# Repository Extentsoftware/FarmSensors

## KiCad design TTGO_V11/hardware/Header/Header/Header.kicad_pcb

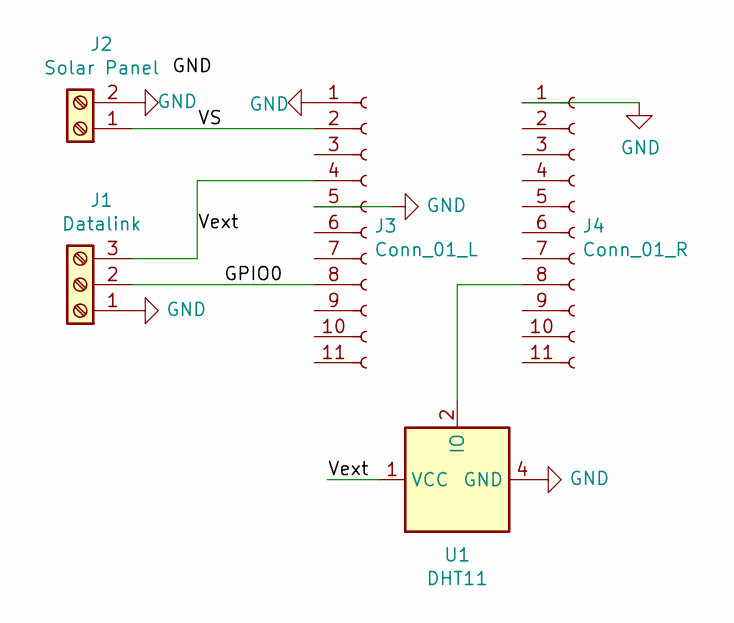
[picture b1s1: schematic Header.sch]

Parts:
J1: Datalink; TerminalBlock_MetzConnect_Type101_RT01603HBWC_1x03_P5.08mm_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
J2: Solar Panel; TerminalBlock_MetzConnect_Type101_RT01602HBWC_1x02_P5.08mm_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
J3: Conn_01_L; PinHeader_1x11_P2.54mm_Vertical
J4: Conn_01_R; PinHeader_1x11_P2.54mm_Vertical
U1: DHT11; Aosong_DHT11_5.5x12.0_P2.54mm

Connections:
/GPIO0: J1.2, J3.8
/VS: J2.1, J3.2
/Vext: J1.3, J3.4, U1.1 (VCC)
GND: J1.1, J2.2, J3.1, J3.5, J4.1, U1.4 (GND)
unnamed: J4.8, U1.2 (IO)

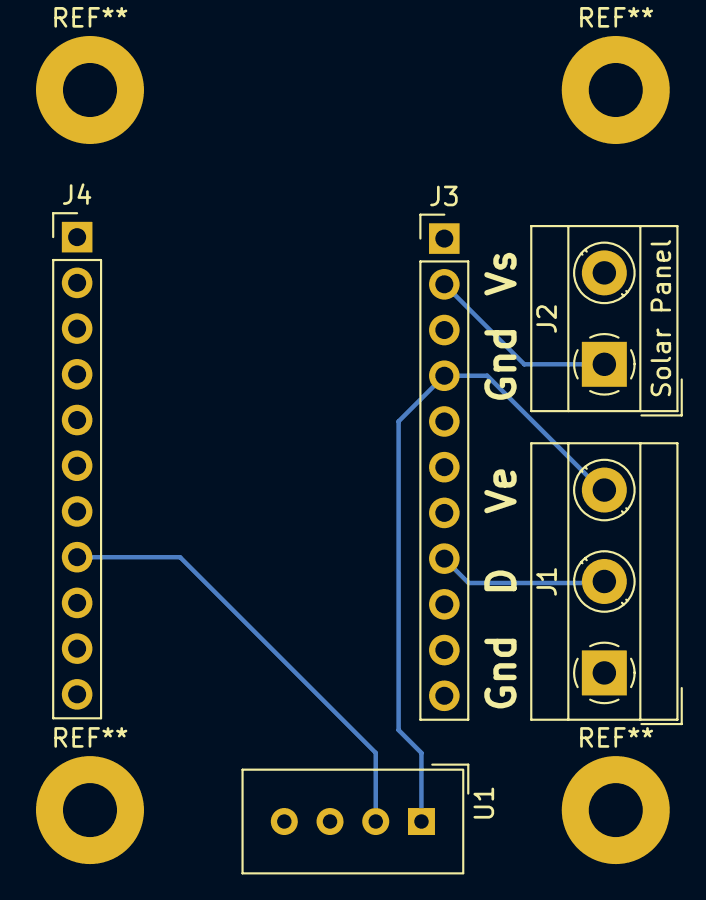
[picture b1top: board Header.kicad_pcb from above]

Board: 2 copper layers, 5 parts (0 on the bottom side), 5 nets.

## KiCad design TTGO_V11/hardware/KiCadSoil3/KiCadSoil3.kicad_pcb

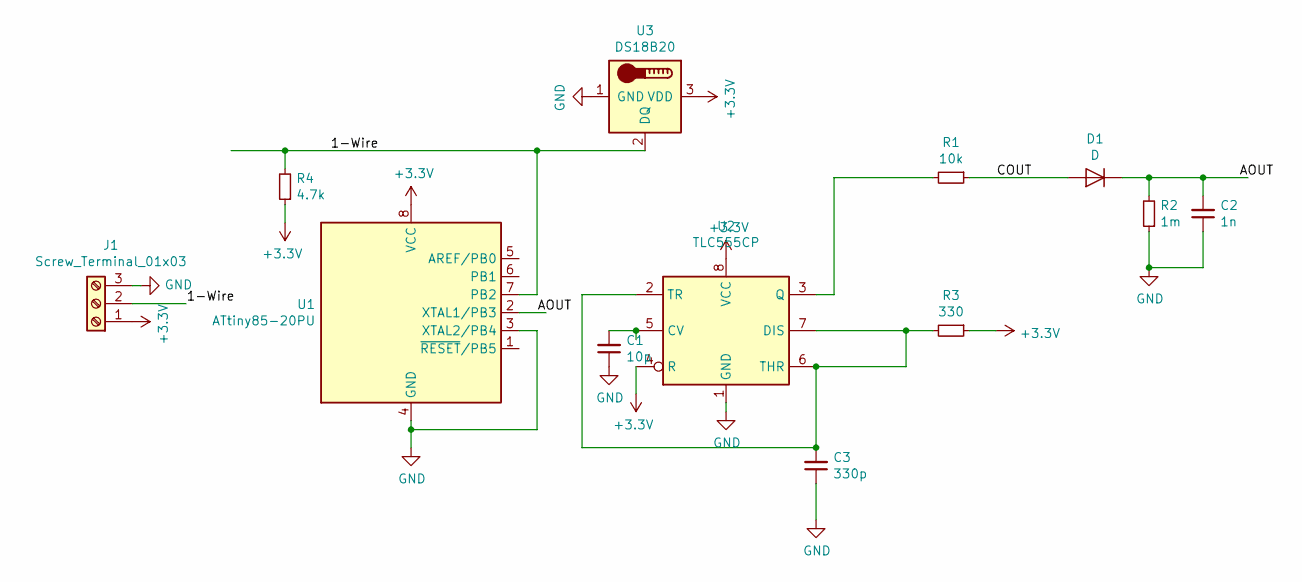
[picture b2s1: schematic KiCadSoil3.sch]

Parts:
C1: 10p; C_Disc_D4.3mm_W1.9mm_P5.00mm
C2: 1n; C_Disc_D4.3mm_W1.9mm_P5.00mm
C3: 330p; C_Disc_D4.3mm_W1.9mm_P5.00mm
D1: D; D_T-1_P5.08mm_Horizontal
J1: Screw_Terminal_01x03; JST_EH_B3B-EH-A_1x03_P2.50mm_Vertical
R1: 10k; R_Axial_DIN0204_L3.6mm_D1.6mm_P7.62mm_Horizontal
R2: 1m; R_Axial_DIN0204_L3.6mm_D1.6mm_P7.62mm_Horizontal
R3: 330; R_Axial_DIN0204_L3.6mm_D1.6mm_P7.62mm_Horizontal
R4: 4.7k; R_Axial_DIN0204_L3.6mm_D1.6mm_P7.62mm_Horizontal
U1: ATtiny85-20PU; DIP-8_W7.62mm
U2: TLC555CP; DIP-8_W7.62mm
U3: DS18B20; TO-92_Inline_Wide

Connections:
+3V3: J1.1, R3.1, R4.1, U1.8 (VCC), U2.4 (R), U2.8 (VCC), U3.3 (VDD)
/1-Wire: J1.2, R4.2, U1.7 (PB2), U3.2 (DQ)
/AOUT: C2.2, D1.1 (K), R2.2, U1.2 (XTAL1/PB3)
/COUT: D1.2 (A), R1.1
GND: C1.1, C2.1, C3.1, J1.3, R2.1, U1.3 (XTAL2/PB4), U1.4 (GND), U2.1 (GND), U3.1 (GND)
unnamed: C1.2, U2.5 (CV)
unnamed: C3.2, R3.2, U2.2 (TR), U2.6 (THR), U2.7 (DIS)
unnamed: R1.2, U2.3 (Q)

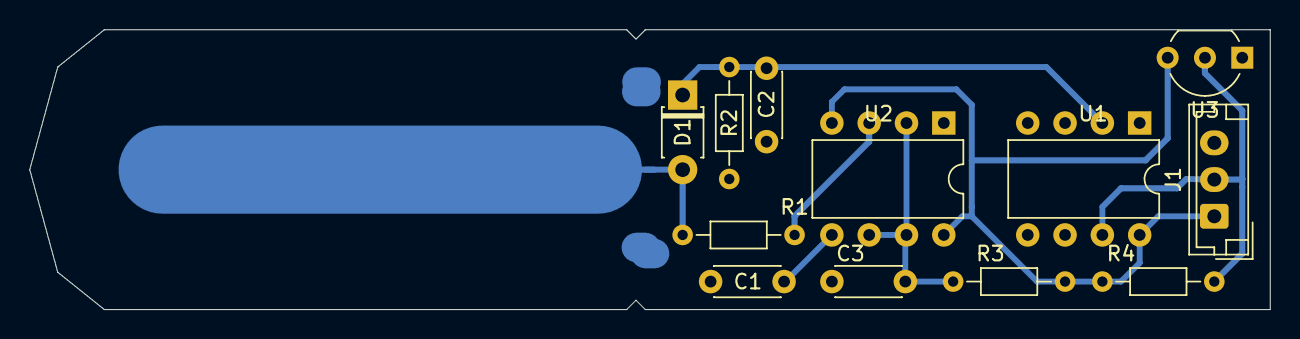
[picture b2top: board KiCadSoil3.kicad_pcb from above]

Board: 2 copper layers, 84.5 x 19.0 mm, 12 parts (0 on the bottom side), 8 nets.

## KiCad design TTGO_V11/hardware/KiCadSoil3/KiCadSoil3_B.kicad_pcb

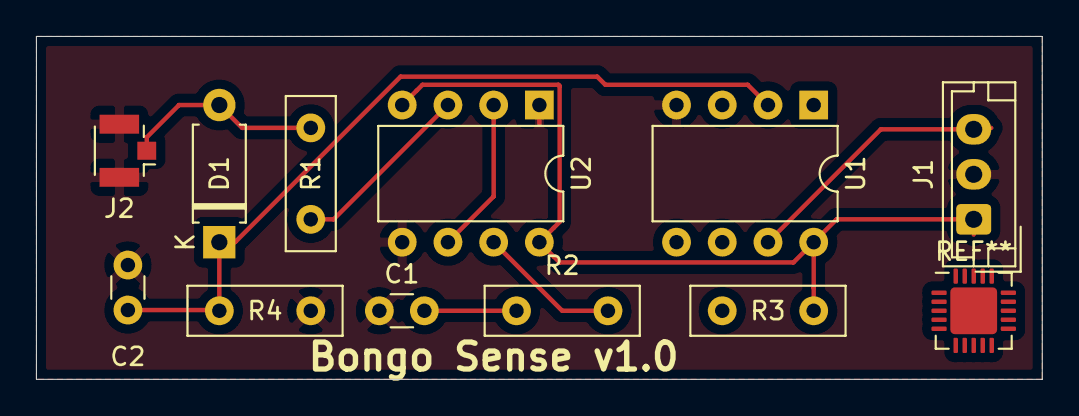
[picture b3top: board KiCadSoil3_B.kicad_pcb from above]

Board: 2 copper layers, 55.9 x 19.1 mm, 11 parts (0 on the bottom side), 9 nets.

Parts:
C1, C2: 660p; C_Disc_D3.0mm_W1.6mm_P2.50mm
D1: D; D_A-405_P7.62mm_Horizontal
J1: Screw_Terminal_01x03; JST_EH_B3B-EH-A_1x03_P2.50mm_Vertical
J2: Conn_Coaxial; U.FL_Hirose_U.FL-R-SMT-1_Vertical
R1: 10k; R_Box_L8.4mm_W2.5mm_P5.08mm
R2: 1.6k; R_Box_L8.4mm_W2.5mm_P5.08mm
R3: 330; R_Box_L8.4mm_W2.5mm_P5.08mm
R4: 1m; R_Box_L8.4mm_W2.5mm_P5.08mm
U1: ATtiny85-20PU; DIP-8_W7.62mm
U2: TLC555CP; DIP-8_W7.62mm

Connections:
+3V3: J1.1, R3.1, U1.8, U2.4, U2.8
/1-Wire: J1.3, U1.7
/AOUT: C2.2, D1.1, R4.2, U1.2
GND: C1.1, C2.1, J1.2, J2.2, R4.1, U1.4, U2.1, U2.5
unnamed: C1.2, R2.1
unnamed: D1.2, J2.1, R1.1
unnamed: R1.2, U2.3
unnamed: R2.2, R3.2, U2.7
unnamed: U2.2, U2.6

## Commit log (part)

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2019-07-03 initial
2019-07-03 started readme
2019-07-04 preferences
2019-07-05 sensor work
2019-07-06 tiny gps work
2019-07-06 fixed build
2019-07-10 sensor
2019-07-10 moved to platformio
2019-07-10 more platform.io work
2019-07-10 platform work
2019-07-10 added library
2019-07-11 change startup modes
2019-07-11 new modes
2019-07-11 typos
2019-07-11 docs
2019-07-12 updated docs
2019-07-12 readme
2019-07-21 library dependencies
2019-07-21 start on sensor UI
2019-07-21 fix radio xmit
2019-07-21 complete web form config
2019-07-21 send diagnostics
2019-07-22 startup modes for hub
2019-07-22 included power settings
2019-07-23 board changes
2019-07-23 fixed defaults
2019-07-25 rearranged lora startup
2019-07-27 testbed
2019-07-28 working 125khz, sf6/cr5
2019-07-28 migrated radio settings to main project
2019-07-28 Adjusted power settings
2019-08-01 hardware changes
2019-08-01 debug
2019-08-02 changed to 15min broadcast
2019-08-05 changed modes on hub
2019-08-06 implemented wifi toggle
2019-08-07 tidyup
2019-08-10 move pwr to gpio4
2019-08-11 sensor changes
2019-08-13 startup changes
2019-08-13 beast 2 setup
2019-08-15 move to i2c
2019-08-16 i2c work
2019-08-21 biard
2019-08-22 wake up time issues
2019-08-30 set correct delay for temp sensor
2019-09-10 reorganise for two TTGO board types
2019-09-10 axp changes
2019-09-11 axp192 work
2019-09-11 power library
2019-09-11 fixed gps wakeup
2019-09-12 power experiments
2019-09-13 gitignore
2019-09-13 power changes
2019-09-13 introduce power into v10 hub
2019-09-13 power changes to the hub
2019-09-13 updated readne
2019-09-15 removed redundant files
2019-09-20 hub version and gps diagnostics
2019-09-24 cleanup
2019-10-13 power mode
2019-10-13 hub wifi timeout
2020-02-25 update libs
2020-03-27 capability
2020-04-25 fix sensors
2020-05-16 Delays
2020-07-08 display changes
2020-07-10 mqtt work
2020-07-16 reorg boards
2020-07-23 add wifi
2020-08-31 added ds18b20
2020-11-20 reconfigure
2020-11-21 header working
2020-11-26 onewire work
2020-12-21 new at85ADC
2020-12-22 added oscillator
2020-12-24 generic adc + frequency counter
2020-12-24 message
2021-01-11 sensor board work
2021-02-21 drill
2021-04-10 new board
2021-04-20 fix hub
2021-04-23 mods
2021-04-26 implement wifi mode
2021-04-28 include dallas
2021-04-28 add dallas
2021-05-15 design changes
2021-05-16 pcb changes
2021-05-18 drill hole changes
2021-06-19 organise folders
2021-06-19 Bump lodash
    Bumps [lodash](https://github.com/lodash/lodash) from 4.17.11 to 4.17.21.
    - [Release notes](https://github.com/lodash/lodash/releases)
    - [Commits](https://github.com/lodash/lodash/compare/4.17.11...4.17.21)
    ---
    updated-dependencies:
    - dependency-name: lodash
2021-06-19 Bump y18n
    Bumps [y18n](https://github.com/yargs/y18n) from 3.2.1 to 3.2.2.
    - [Release notes](https://github.com/yargs/y18n/releases)
    - [Changelog](https://github.com/yargs/y18n/blob/master/CHANGELOG.md)
    - [Commits](https://github.com/yargs/y18n/commits)
    ---
    updated-dependencies:
2021-06-19 Bump hosted-git-info
    Bumps [hosted-git-info](https://github.com/npm/hosted-git-info) from 2.7.1 to 2.8.9.
    - [Release notes](https://github.com/npm/hosted-git-info/releases)
    - [Changelog](https://github.com/npm/hosted-git-info/blob/v2.8.9/CHANGELOG.md)
    - [Commits](https://github.com/npm/hosted-git-info/compare/v2.7.1...v2.8.9)
    ---
    updated-dependencies:
2021-06-19 Bump handlebars
    Bumps [handlebars](https://github.com/wycats/handlebars.js) from 4.0.12 to 4.7.7.
    - [Release notes](https://github.com/wycats/handlebars.js/releases)
    - [Changelog](https://github.com/handlebars-lang/handlebars.js/blob/master/release-notes.md)
    - [Commits](https://github.com/wycats/handlebars.js/compare/v4.0.12...v4.7.7)
    ---
    updated-dependencies:
2021-06-19 Bump ws
    Bumps [ws](https://github.com/websockets/ws) from 5.2.2 to 5.2.3.
    - [Release notes](https://github.com/websockets/ws/releases)
    - [Commits](https://github.com/websockets/ws/compare/5.2.2...5.2.3)
    ---
    updated-dependencies:
    - dependency-name: ws
2021-06-19 remove old dirs
2021-06-19 Bump lodash in /src/server/docker/grafana/plugins/grafana-worldmap-panel
    Bumps [lodash](https://github.com/lodash/lodash) from 4.17.11 to 4.17.21.
    - [Release notes](https://github.com/lodash/lodash/releases)
    - [Commits](https://github.com/lodash/lodash/compare/4.17.11...4.17.21)
    ---
    updated-dependencies:
    - dependency-name: lodash
2021-06-19 Bump ws in /src/server/docker/grafana/plugins/grafana-worldmap-panel
    Bumps [ws](https://github.com/websockets/ws) from 5.2.2 to 5.2.3.
    - [Release notes](https://github.com/websockets/ws/releases)
    - [Commits](https://github.com/websockets/ws/compare/5.2.2...5.2.3)
    ---
    updated-dependencies:
    - dependency-name: ws
2021-06-19 Bump y18n in /src/server/docker/grafana/plugins/grafana-worldmap-panel
    Bumps [y18n](https://github.com/yargs/y18n) from 3.2.1 to 3.2.2.
    - [Release notes](https://github.com/yargs/y18n/releases)
    - [Changelog](https://github.com/yargs/y18n/blob/master/CHANGELOG.md)
    - [Commits](https://github.com/yargs/y18n/commits)
    ---
    updated-dependencies:
2021-06-19 more updates
2021-08-05 Bump tar in /src/server/docker/grafana/plugins/grafana-worldmap-panel
    Bumps [tar](https://github.com/npm/node-tar) from 4.4.8 to 4.4.15.
    - [Release notes](https://github.com/npm/node-tar/releases)
    - [Changelog](https://github.com/npm/node-tar/blob/main/CHANGELOG.md)
    - [Commits](https://github.com/npm/node-tar/compare/v4.4.8...v4.4.15)
    ---
    updated-dependencies:
2021-08-13 Bump path-parse
    Bumps [path-parse](https://github.com/jbgutierrez/path-parse) from 1.0.6 to 1.0.7.
    - [Release notes](https://github.com/jbgutierrez/path-parse/releases)
    - [Commits](https://github.com/jbgutierrez/path-parse/commits/v1.0.7)
    ---
    updated-dependencies:
    - dependency-name: path-parse
2021-08-15 change constants
2021-08-25 fixes for 1wire
2021-09-01 noise cancelling mode
2021-09-01 Low noise updates
2021-09-01 reliability updates
2021-09-02 Bump tar in /src/server/docker/grafana/plugins/grafana-worldmap-panel
    Bumps [tar](https://github.com/npm/node-tar) from 4.4.8 to 4.4.19.
    - [Release notes](https://github.com/npm/node-tar/releases)
    - [Changelog](https://github.com/npm/node-tar/blob/main/CHANGELOG.md)
    - [Commits](https://github.com/npm/node-tar/compare/v4.4.8...v4.4.19)
    ---
    updated-dependencies:
2021-09-14 added locatin and distance
2021-09-14 updates for geohash
2021-09-22 Bump tmpl in /src/server/docker/grafana/plugins/grafana-worldmap-panel
    Bumps [tmpl](https://github.com/daaku/nodejs-tmpl) from 1.0.4 to 1.0.5.
    - [Release notes](https://github.com/daaku/nodejs-tmpl/releases)
    - [Commits](https://github.com/daaku/nodejs-tmpl/commits/v1.0.5)
    ---
    updated-dependencies:
    - dependency-name: tmpl
2021-10-16 latest changes
2021-10-16 print id
2021-10-19 rework Hub
2021-10-24 minor changes
2021-11-01 fix sensor id
2021-12-08 changes for econet
2021-12-14 gps changes
2021-12-15 update dashboard
2021-12-17 improve message handling
2021-12-25 updates to hub
2021-12-25 sim changes
2021-12-26 fixes
2021-12-29 updtes
2022-01-04 library updates
2022-01-05 fixes for reliability
2022-01-17 resilience changes
2022-02-13 Bump ajv in /src/server/docker/grafana/plugins/grafana-worldmap-panel
    Bumps [ajv](https://github.com/ajv-validator/ajv) from 6.5.5 to 6.12.6.
    - [Release notes](https://github.com/ajv-validator/ajv/releases)
    - [Commits](https://github.com/ajv-validator/ajv/compare/v6.5.5...v6.12.6)
    ---
    updated-dependencies:
    - dependency-name: ajv
2022-04-09 Bump moment in /src/server/docker/grafana/plugins/grafana-worldmap-panel
    Bumps [moment](https://github.com/moment/moment) from 2.22.2 to 2.29.2.
    - [Release notes](https://github.com/moment/moment/releases)
    - [Changelog](https://github.com/moment/moment/blob/develop/CHANGELOG.md)
    - [Commits](https://github.com/moment/moment/compare/2.22.2...2.29.2)
    ---
    updated-dependencies:
2022-04-19 pcb manufacture
2022-04-19 Added repeater
2022-04-21 box for repeater
2022-04-23 added new hub code
2022-04-25 move to TTGO Lora32
2022-04-29 fixes for sim
2022-04-29 Bump async in /src/server/docker/grafana/plugins/grafana-worldmap-panel
    Bumps [async](https://github.com/caolan/async) from 2.6.1 to 2.6.4.
    - [Release notes](https://github.com/caolan/async/releases)
    - [Changelog](https://github.com/caolan/async/blob/v2.6.4/CHANGELOG.md)
    - [Commits](https://github.com/caolan/async/compare/v2.6.1...v2.6.4)
    ---
    updated-dependencies:
2022-05-05 get sim working in Austria
2022-05-07 build too big
2022-05-08 bluetooth
2022-05-08 BLE Server
2022-05-08 client work
2022-05-09 more BLE work
2022-05-11 more work on ble
2022-05-11 more BLE
2022-05-25 radio changes
2022-05-25 Hub updates
2022-05-31 added loraempty
2022-06-18 fix for spi
2022-06-18 test work
2022-06-19 fix connection
2022-06-26 fix lora
2022-07-06 enable bluetooth
2022-07-06 add gps
2022-07-06 updates to status
2022-07-08 Bump moment in /src/server/docker/grafana/plugins/grafana-worldmap-panel
    Bumps [moment](https://github.com/moment/moment) from 2.22.2 to 2.29.4.
    - [Release notes](https://github.com/moment/moment/releases)
    - [Changelog](https://github.com/moment/moment/blob/develop/CHANGELOG.md)
    - [Commits](https://github.com/moment/moment/compare/2.22.2...2.29.4)
    ---
    updated-dependencies:
2022-07-09 updates to gps
2022-11-11 Bump loader-utils
    Bumps [loader-utils](https://github.com/webpack/loader-utils) from 1.1.0 to 1.4.2.
    - [Release notes](https://github.com/webpack/loader-utils/releases)
    - [Changelog](https://github.com/webpack/loader-utils/blob/v1.4.2/CHANGELOG.md)
    - [Commits](https://github.com/webpack/loader-utils/compare/v1.1.0...v1.4.2)
    ---
    updated-dependencies:
2022-11-11 Bump minimatch
    Bumps [minimatch](https://github.com/isaacs/minimatch) from 3.0.4 to 3.1.2.
    - [Release notes](https://github.com/isaacs/minimatch/releases)
    - [Commits](https://github.com/isaacs/minimatch/compare/v3.0.4...v3.1.2)
    ---
    updated-dependencies:
    - dependency-name: minimatch
2022-11-20 comments
2022-11-20 led off
2022-11-20 led changes
2022-12-07 Bump decode-uri-component
    Bumps [decode-uri-component](https://github.com/SamVerschueren/decode-uri-component) from 0.2.0 to 0.2.2.
    - [Release notes](https://github.com/SamVerschueren/decode-uri-component/releases)
    - [Commits](https://github.com/SamVerschueren/decode-uri-component/compare/v0.2.0...v0.2.2)
    ---
    updated-dependencies:
    - dependency-name: decode-uri-component
2022-12-12 Bump qs in /src/server/docker/grafana/plugins/grafana-worldmap-panel
    Bumps [qs](https://github.com/ljharb/qs) from 6.5.2 to 6.5.3.
    - [Release notes](https://github.com/ljharb/qs/releases)
    - [Changelog](https://github.com/ljharb/qs/blob/main/CHANGELOG.md)
    - [Commits](https://github.com/ljharb/qs/compare/v6.5.2...v6.5.3)
    ---
    updated-dependencies:
2023-05-16 try heltec board
2023-05-22 updates to use i2c
2023-05-22 minor update to remove old code
2023-05-23 change display msg
2023-06-05 update msg
2023-08-25 added bme280
2023-08-28 bme280 additions
2023-08-28 additions
2023-08-31 BME280 work
2023-09-05 server changes
2023-09-22 add bme code
2023-10-15 turn off debg
2023-10-16 fix sensor list
2024-03-30 docker updates
2024-04-02 reoganise directories
2024-04-03 change path
2024-04-03 ingree changes
2024-04-05 reorganise directories
2024-04-11 new server
2024-04-17 TTGO Beam + microk8 work
2024-04-17 update SSID
2024-04-17 added missing header
2024-04-17 Remove old passwords
2024-04-17 split bongofn from servers
2024-05-05 update sensor profile
2024-05-05 apply changes
2024-05-06 complete bongofn config
2024-05-07 Upgrade sensor images
2024-05-15 kubernettes updates
2024-05-15 update certificate
2024-05-16 add letsencrypt issuer
2024-06-23 update version
2024-10-07 update library
2024-10-13 fix certificate issuer
2024-10-14 fix file size limits and ingress
2024-12-14 minor fixes
2024-12-22 remove unused file
2025-05-26 update libraries
2025-06-17 add wire setup
2025-10-27 scmitt work
2025-10-28 cubecell updates
2026-03-27 Update farm scout
